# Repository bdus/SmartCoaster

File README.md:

# Smart Coaster — AI 驱动的硬件研发流水线

> 一个真实产品（智能饮水杯垫）为载体，建立 **本地 AI Agent + 参数化设计 + 自动化验证 + 数字样机可视化** 的硬件研发流程。
>
> **当前（2026-11-04，去灯 / 2 层收口轮）**：
> - **产品定义变更（以此为准）**：LED 与所有发光件全部去掉；PCB 最多 2 层。前脸只有 **26×7 屏窗 + 按键**，唯一缝隙是**顶板-底座 0.5 mm 浮动缝**（秤的行程缝）；无灯、无灯缝。
> - **P1 设计闭环**：方形 B 机械 **12 件 21/21**（37 组干涉 0）；原理图 **43 器件 / 28 网络**、ERC 0 error；**2 层 PCB 已布通：`kicad-cli pcb drc --severity-all` 0 violation / 0 unconnected**（576 track + 62 via，证据 `electronics/kicad/build/DRC_2l.rpt`；47 footprint = 43 器件 + 4 安装孔）；固件 ESP-IDF v6.1，灯效代码已删（测试计数见 `docs/HANDOFF.md`）。
> - **P2 可制造**：2 层 Gerber/钻孔/坐标/zip（`build/gerbers/`）、JLC 2 层 DFM **全 PASS**（`build/DFM.md`）、BOM（43 器件 / 24 行）；拼板建议 2×2 V-groove。
> - **P3 红点水平**：CMF 4 变体、120×120×36 包装、产品叙事、**Red Dot 2026 提交包**（`submission/`），渲染已全部按“无灯”重出。
> - **仍需用户动手**：采购 ESP32-S3-DevKitC-1 / 0.91" OLED / HY928D / HX711 模块 / 砝码，按 `docs/09` 装配并按 `tests/handboard/BRINGUP_RECORD.md` 标定；PCB 打样与 3D 打印下单。
> - **下一阶段（2026-11-04 用户新指示）**：冻结结构与功能，只做**外观变体**。功能确认：**方形 square_v1 正常（21/21，与当前电子/固件一致）**；**圆形 LUMEN 为旧概念（光导/LED/0.49" 屏/无按键）→ 不能直接当外观变体**；当前方形 PCB 对角线 131.8 mm > Ø110，**真圆需重做 PCB（功能变更）**。计划见 [`docs/13_Appearance_Variants_Plan.md`](docs/13_Appearance_Variants_Plan.md)，验收经验见 [`docs/01` §16](docs/01_AI_Hardware_Engineering_Pipeline.md)。
> - **报告与审计（2026-11-04）**：[技术报告](docs/REPORT_技术报告.md) · [成果展示](docs/REPORT_成果展示.md) · 逐条审计 [PRD](docs/AUDIT_PRD.md) / [流水线](docs/AUDIT_PIPELINE.md) / [环境](docs/AUDIT_ENV.md) · [独立验收](docs/VERIFY_REPORT.md) · **电路** [S2 仿真](docs/S2_CIRCUIT_SIM.md) / [电气评审](docs/REVIEW_ELECTRICAL.md) / [电气验证矩阵](docs/VERIFICATION_ELECTRICAL.md)
> - **EasyEDA 第二实现（2026-11-05）**：工具装到 `/data/Documents/tools/`（easyeda-agent **v1.16.0** / LCEDA Pro **4.1.97** / 官方 eprj3 skill **2.2.1**）；新建 [`electronics/easyeda/`](electronics/easyeda/README.md)，从冻结 KiCad 设计重建 `.eprj3`：**47 器件 / 7 块 / 28 网络 / 168 连接脚与 KiCad 逐脚一致**、5 门禁 + netcheck 全绿；**2 层铜（576 track + 62 via）从已验证 KiCad 布线 1:1 移植**，独立 GEOS 检查 C1–C5 全 PASS。**客户端 live DRC/铺铜/Gerber 仍被登录/激活墙阻塞**（`pro.lceda.cn` 对本机 418）；技术栈调研见 [`docs/EDA_TOOLCHAIN_SURVEY.md`](docs/EDA_TOOLCHAIN_SURVEY.md)。

## 结果一览

| 层 | 状态 |
|---|---|
| 提交包 | `submission/`：4 张主图 + A3 故事页（Red Dot 2026），无灯版 |
| 包装 | 120×120×36 天地盖 + 纸浆内衬 + 腰封；3D + 3 张渲染 |
| CMF | 4 个配色变体（Lumen Violet / Moss / Sand / Graphite）+ `render/cmf/CMF_variants.png` + `docs/10_CMF_and_Packaging.md` |
| 机械 | **方形 B 12 件 21/21**（当前功能基线，前脸 26×7 屏窗 + 按键，0.5 mm 浮动缝）；LUMEN 圆形 21/21 但为**旧概念**（含已删光导/LED、0.49" 屏、无按键），只作外观语言参考 |
| FEA | HY928D 5 kg 中心 **0.3435 mm**（k≈142.8 N/mm）、支反力 100%、+y 两颗 99.4%、非奇异热点 468 MPa |
| 电路 | ngspice：3.956 mV → 0.506 V（×128）；HX711 3.3 V 满量程 ±12.9 mV（30.7%）；**S2 四模块×六类分析 28 结果（21 PASS / 7 个真实发现）** |
| PCB | 主方案 **2 层已布通**：**43 器件 / 28 网络**（删 LED 13 + TP 6）；47 footprint、576 track + 62 via；**0 DRC / 0 unconnected**（`build/DRC_2l.rpt`）；官方 S3-MINI-1 封装（U1 与机械对齐） |
| EasyEDA 第二实现 | [`electronics/easyeda/`](electronics/easyeda/README.md)：`.eprj3`（原理图 + 已布线 2 层 PCB）47 器件 / 28 网络 / 168 连接脚与 KiCad 对账一致，5 门禁 + netcheck 全绿；铜 576 track + 62 via 由已验证 KiCad 布线移植，独立 C1–C5 几何检查全 PASS；**无铺铜 / 无客户端保存回读 / 无 Gerber**，client live 待登录；工具与限制见 [`/data/Documents/tools/EASYEDA_INSTALL_NOTES.md`](../../tools/EASYEDA_INSTALL_NOTES.md) |
| 固件 | ESP-IDF v6.1 build 通过（**519,184 B / 507 KiB**，含 NVS + NimBLE GATT 0xFF00 + 时间/跨日 + 中文 UI；删 halo 后 −13.8 KB）；host 11/11 + mock 9/9 + C↔Python 差分 16/16；PM light sleep + BLE modem sleep；**连续采样功耗预算 5.02 mA → 约 4.2 天**（S2 仿真），7 天需模拟前端占空（待固件） |
| 渲染 | Blender 4.5.3 LTS：方形 B 4 张（外观/正视/PCB 细节/爆炸图）+ CMF 4 变体 + 包装 3 张；无灯、无发光件 |
| 仿真工具 | ccx 2.22 + gmsh 4.13.1（FreeCAD 自带）、ngspice 36、QEMU 9.2.2、Blender 4.5.3 |
| IP 印花多材料 | `appearance/`：Kromacut 4.2.0 印花→多材料几何、外壳开槽、Blender 数字样机、Bambu 床面排版 3MF；**18 个可打印 STL（打印姿态：印花正面贴床/第一层、按钮躺平、无需支撑）**，140/140 只读验收 |
| 可复用 Agent 系统 | `agent-system/`：8 角色 / 28 阶段 / 7 组 145 条门禁 / 9 模板 / 脚手架 + 自校验；`check_system.py` PASS，`new_project.py` 15/15 |

## 目录

```
SmartCoaster/
├── docs/                  01 流程（含 §16 验收经验）· 02 PRD · 05–13 设计文档 · HANDOFF · AUDIT_* · VERIFY · REPORT_*
├── ref/                   原始图纸/照片/PDF + 无损 Markdown 转录
├── config/                参数与验收阈值
├── mechanical/
│   ├── lumen/             圆形 LUMEN（Ø110×17，概念线，13 零件）
│   ├── square_v1/         方形 B（100×100×18，12 零件，无灯）
│   ├── hy928d/            HY928D 传感器 v2（PROVISIONAL 重建）
│   ├── legacy/ original_cad/
├── electronics/           pinmap/电源树 · kicad/（原理图/PCB/BOM）· easyeda/（EasyEDA 第二实现）· simulation/（ngspice）
├── firmware/              model/（Python 参考）· esp32/（ESP-IDF）· wokwi/（可选）
├── simulation/            mechanical/hy928d/（FEA 网格/结果/云图）
├── tests/firmware/        C host 测试 + C↔Python 差分
├── tests/handboard/       手板 bring-up 记录表
├── submission/            Red Dot 2026 提交包（4 图 + A3 故事页）
├── render/                Blender 场景（square_b / lumen / cmf / packaging）
│   └── print/             3D 打印交付：stl/（18 个打印姿态 STL）+ appearance/（3MF/参考图/manifest）
├── appearance/            IP 印花多材料线：方法/规范/素材/印花几何/开槽/渲染/打印交付
├── agent-system/          可复用 Agent 系统：SYSTEM.yaml + roles/workflows/gates/templates/scripts
├── packaging/             包装参数化模型 + STEP/STL
├── scripts/ build/
```

## 两条产品线（几何互相独立）

| | 圆形 LUMEN | 方形 B |
|---|---|---|
| 目录 | `mechanical/lumen/` | `mechanical/square_v1/` |
| 外形 | Ø110 × 17 | 100 × 100 × 18 |
| 零件 | 13（概念线，不再推进） | **12**（13→12，删发光件） |
| 自检 | **21/21**，38 组干涉 0 | **21/21**，37 组干涉 0 |
| 特征 | 圆形概念（发光方案已废弃） | 0.91" 128×32（窗 26×7）、单键；前脸只有屏窗 + 按键，0.5 mm 浮动缝 |
| 体积/质量 | 63,796.9 mm³ / 129.8 g | 78,338.1 mm³ / 155.3 g |

> 14 mm 概念装不下 12 mm 高的 OLED 模组；普通版按 18 mm 方形，14 mm 留给极简方向。

## 快速开始

```bash
# 机械
cd mechanical/square_v1 && .venv/bin/python cad/export_v01.py && .venv/bin/python cad/verify_v01.py
cd mechanical/lumen     && .venv/bin/python cad/export_v01.py && .venv/bin/python cad/verify_v01.py

# 传感器重建
cd mechanical/hy928d && /data/Documents/tools/agentcad-venv/bin/python src/hy928d_v2.py

# 电路
cd electronics/kicad/scripts && ./build.sh            # 原理图/布线/DRC/BOM/Gerber/DFM 全流程

# 固件
bash tests/firmware/run_host_tests.sh
PYTHONPATH= /data/Documents/tools/sim-venv/bin/pytest firmware/model -q

# 渲染（无灯版）
/data/Documents/tools/blender/blender -b --python render/square_b/build_scene.py
/data/Documents/tools/blender/blender -b --python render/packaging/build_scene.py
python3 render/cmf/make_variants.py                   # 4 配色 + 拼图
python3 submission/make_story.py                      # A3 故事页（先放好 01–04 图）
```

## 关键文档

- [流程 V1.1（含仿真工程 / MCP 编排）](docs/01_AI_Hardware_Engineering_Pipeline.md)
- [产品需求 PRD](docs/02_Smart_Coaster_PRD.md)
- [可行性验证与 bring-up 计划](docs/05_Bringup_and_Verification_Plan.md)
- [固件架构（HAL + Mock + 主机测试）](docs/06_Firmware_Architecture.md)
- [B 版交互设计](docs/design/2026-11-04-ui-interaction-b-design.md)
- [CMF 与包装](docs/10_CMF_and_Packaging.md) · [产品叙事](docs/11_Product_Narrative.md)
- [HY928D 图纸转录](ref/HY928D_5kg_称重传感器_图纸转录.md) / [HX711](ref/HX711_数据手册_海芯.md) / [Hydrate 参考](ref/Hydrate_AI_拆解与结构参考.md)
- [环境安装记录](docs/环境安装记录-agentcad-freecad.md) · [两版交付说明](docs/交付说明-两个版本.md)
- [IP 印花 → 多材料一体打印（方法/工程要求）](appearance/README.md) · [3D 打印交付规范](appearance/PRINT_DELIVERY_SPEC.md)
- **一键编译**：[输入清单](appearance/INPUTS.md) · [唯一配置](appearance/config/appearance_project.yaml) · [`bash appearance/compile.sh`](appearance/compile.sh) · [Agent 提示词](appearance/AGENT_PROMPT.md)
- [可复用 Agent 系统（下一项目起点）](agent-system/README.md) · [本项目证据映射](agent-system/MAPPING_SMARTCoaster.md)

## 路线

- [产品路线：先“能用”，再“红点级”](docs/07_Product_Roadmap.md)

## 待办

- **PCB 2 层已收口**：**0 DRC / 0 unconnected**（`build/DRC_2l.rpt`）+ 2 层 Gerber/钻孔/坐标/zip（`build/gerbers/`）+ JLC 2 层 DFM 全 PASS（`build/DFM.md`）+ 布线预览 `build/pcb_2l.png`。
- 手板采购：ESP32-S3-DevKitC-1、0.91" 128×32 OLED、HY928D、HX711 模块、砝码；按 `docs/05` 矩阵测。
- 固件：BLE GATT、NVS/跨日、低功耗休眠、OLED 中文（灯效代码已删）。
- 渲染：KiCad 3D（待 3D 模型）、3D 打印参考图（拆分/方向/支撑）。

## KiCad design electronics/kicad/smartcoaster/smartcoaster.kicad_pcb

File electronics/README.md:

# electronics/

电路设计（KiCad 9.0.9）。**当前状态（2026-11-04）：43 器件 / 28 网络，ERC 0 error/0 warning；2 层 PCB 已布通，`kicad-cli pcb drc --severity-all` 0 DRC / 0 unconnected；Gerber/钻孔/坐标/DFM 已出。**

- `kicad/` KiCad 工程（原理图、网表、2 层 PCB、BOM、制造文件）——**唯一主链交付，未改动**
- `easyeda/` **EasyEDA Pro 第二实现（2026-11-05）**：`.eprj3` 原理图 + PCB placement，47 器件/28 网络/168 连接脚与 KiCad 逐脚一致；离线 5 门禁全绿，**无铜**；客户端 live 链路待登录/激活。见 [`easyeda/README.md`](easyeda/README.md)、[`easyeda/REPORT.md`](easyeda/REPORT.md)
- `kicad/scripts/` 唯一来源：`design.py`（原理图）、`gen_pcb.py`（未布线 PCB）、`route_2l.sh`（Freerouting 布线 + DRC）
- `simulation/` ngspice 网表与结果：`hy928d_frontend.cir` + `.json`（桥路 + HX711 行为前端，DC/AC；电源/噪声/蒙特卡洛仍是 GAP）
- `pinmap.md` 引脚与电源树（无 LED/光导）

关键证据：`kicad/build/DRC_2l.rpt`（0/0）、`kicad/build/ERC.rpt`（0/0）、`kicad/build/DFM.md`（JLC 2 层全 PASS）、`kicad/build/gerbers/`。

依据：`docs/02_Smart_Coaster_PRD.md` §5、`docs/HANDOFF.md`、`ref/HX711_数据手册_海芯.md` §14。

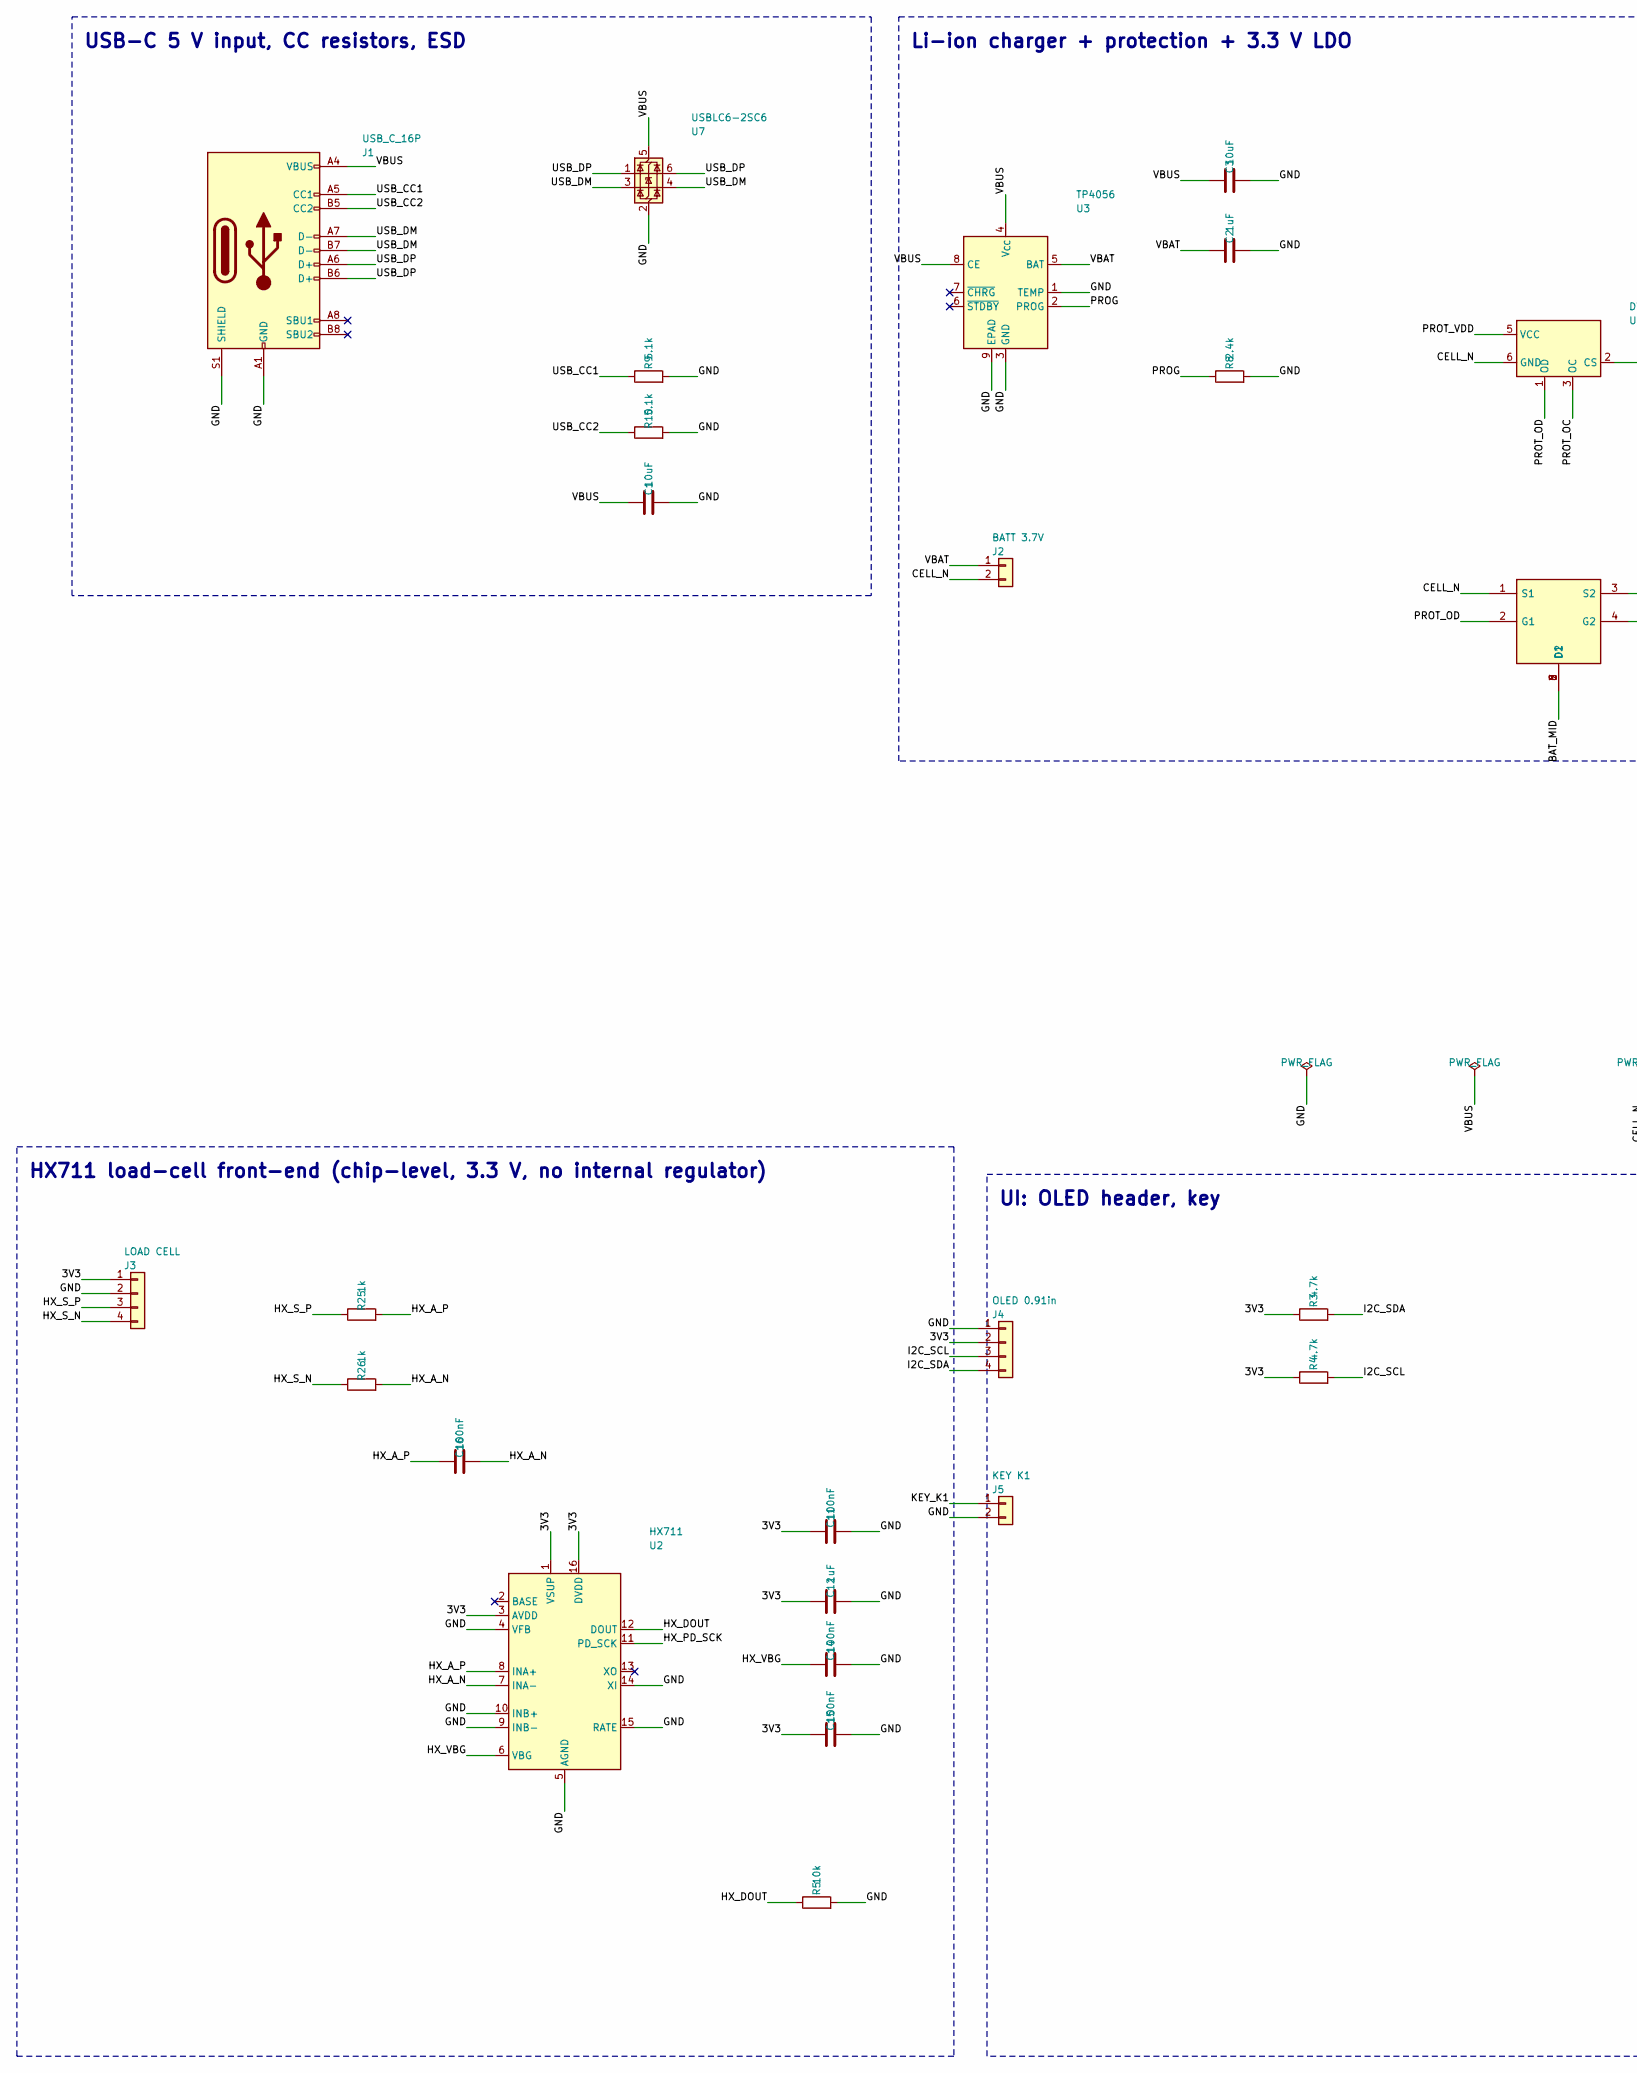
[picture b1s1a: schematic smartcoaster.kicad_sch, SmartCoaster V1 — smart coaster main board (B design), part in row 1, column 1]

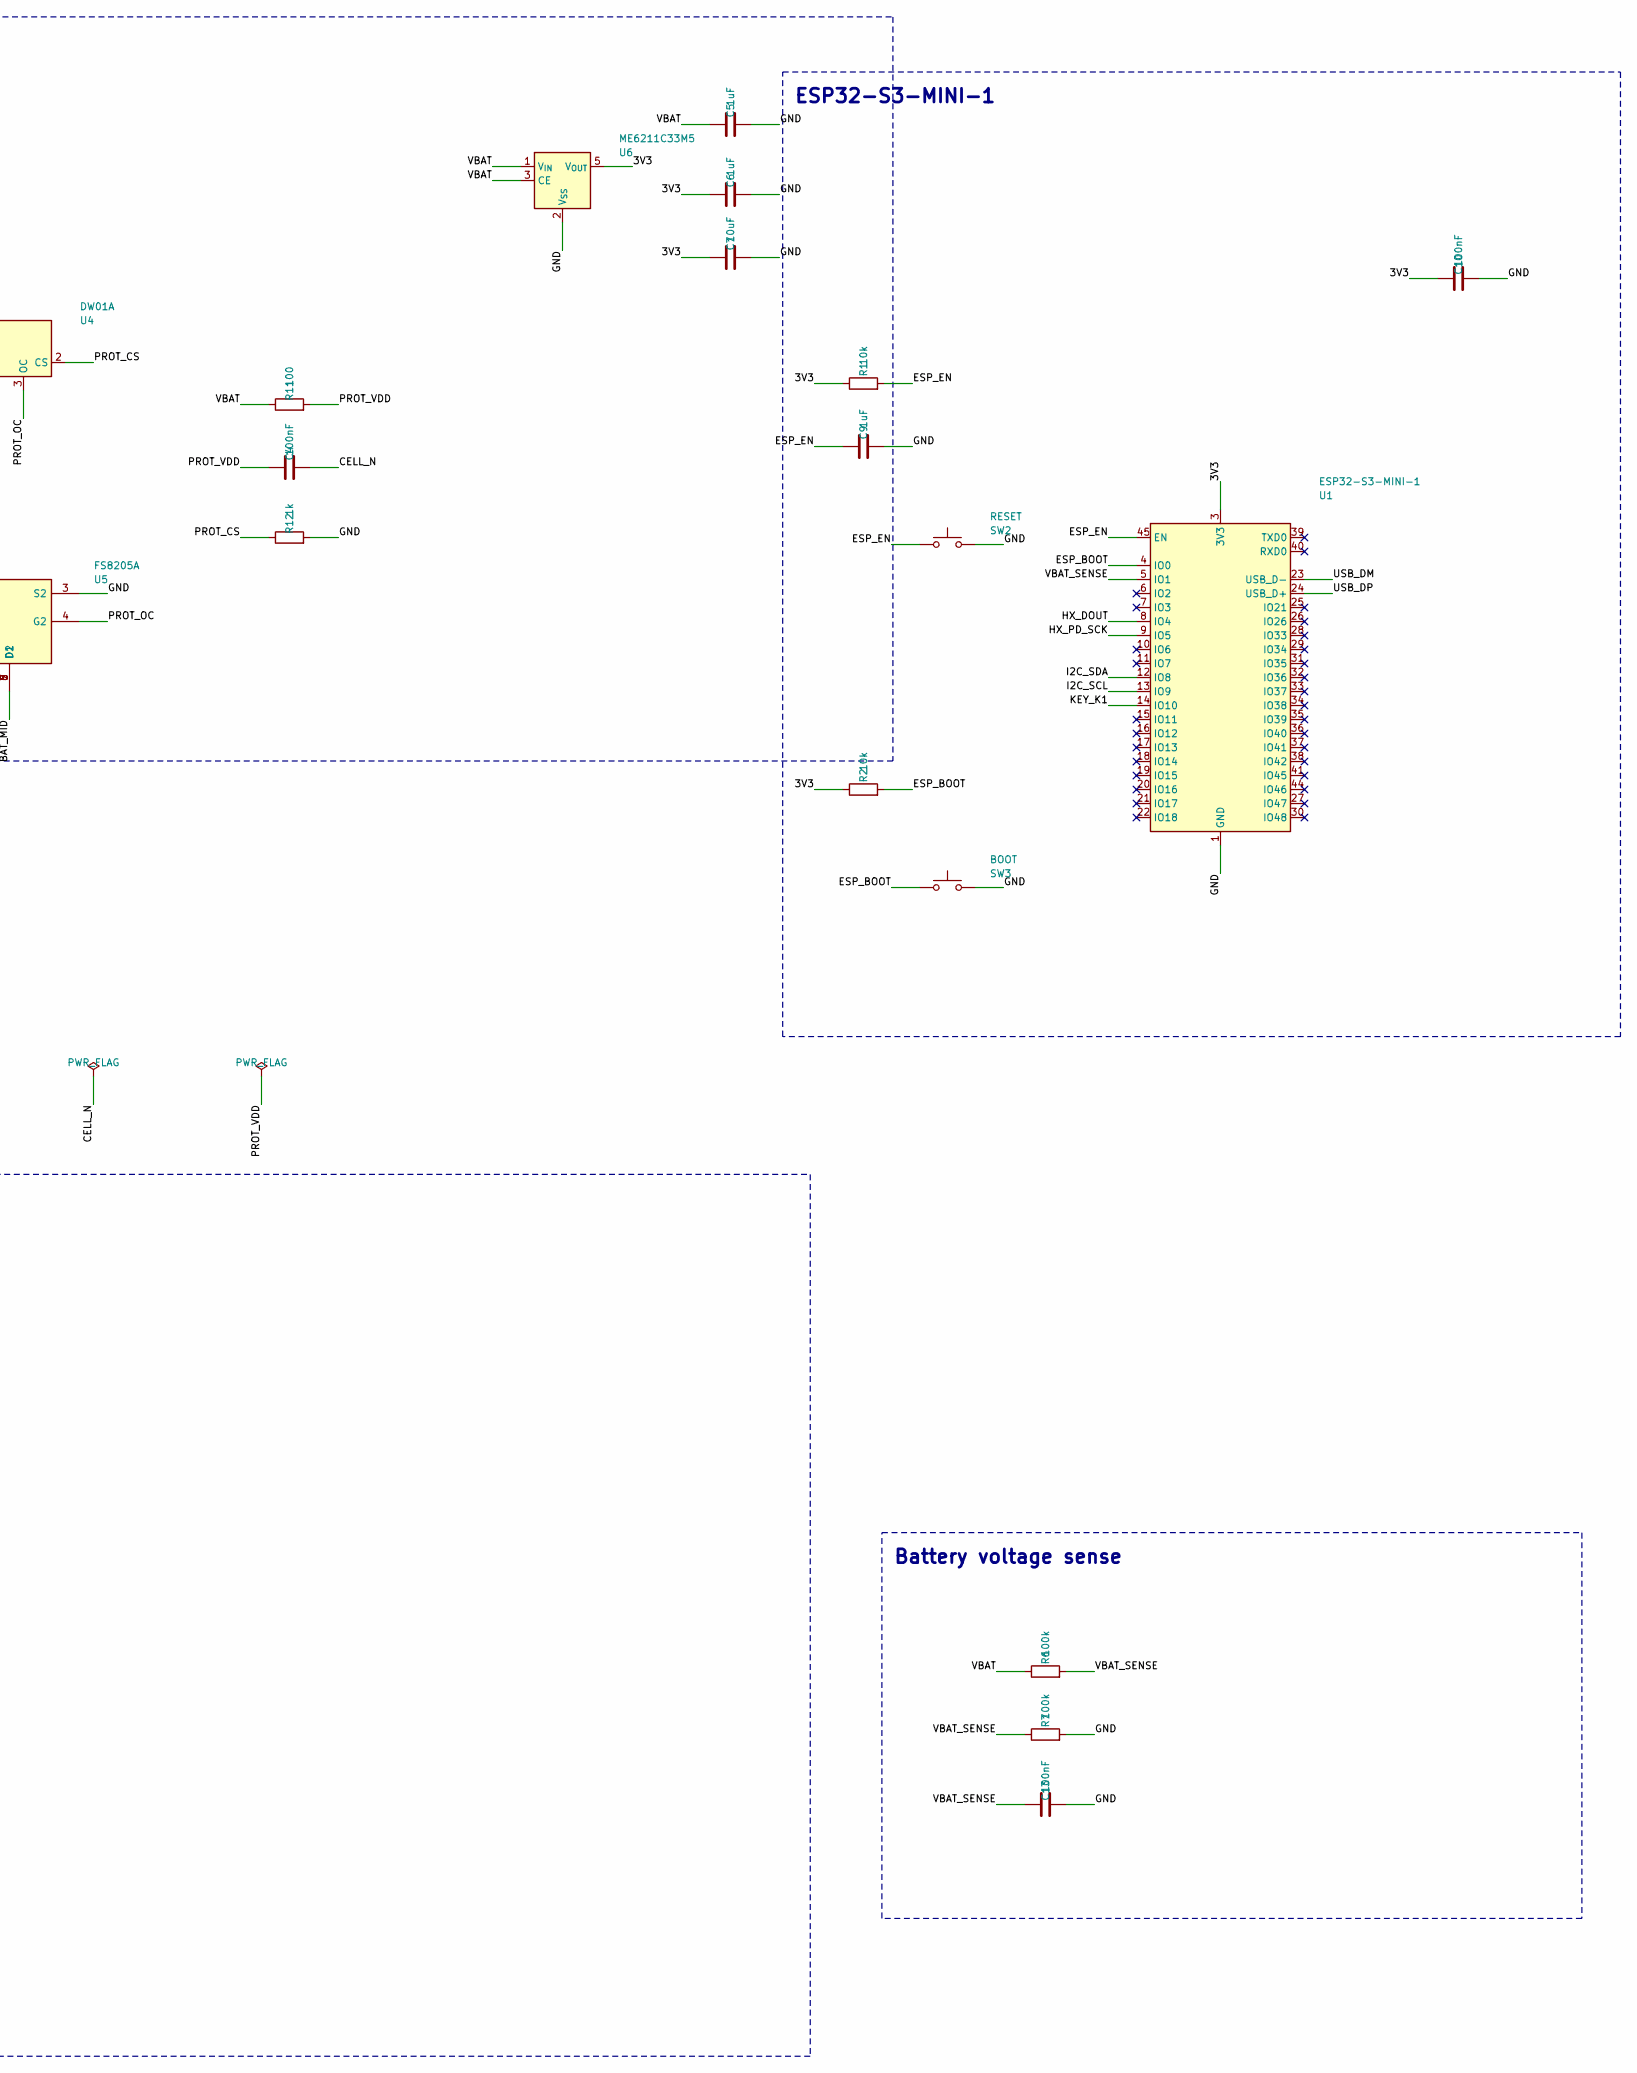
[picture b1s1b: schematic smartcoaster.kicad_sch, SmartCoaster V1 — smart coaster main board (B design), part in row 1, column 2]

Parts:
C1, C3, C7: 10uF; C_0805_2012Metric
C2, C5, C6, C9, C12: 1uF; C_0603_1608Metric
C4, C10, C11, C13, C14, C15, C16: 100nF; C_0603_1608Metric
J1: USB_C_16P; USB_C_Receptacle_HRO_TYPE-C-31-M-12
J2: BATT 3.7V; JST_PH_B2B-PH-K_1x02_P2.00mm_Vertical
J3: LOAD CELL; JST_SH_BM04B-SRSS-TB_1x04-1MP_P1.00mm_Vertical
J4: OLED 0.91in; PinHeader_1x04_P2.54mm_Vertical
J5: KEY K1; JST_PH_B2B-PH-K_1x02_P2.00mm_Vertical
R1, R2, R5: 10k; R_0603_1608Metric
R3, R4: 4.7k; R_0603_1608Metric
R6, R7: 100k; R_0603_1608Metric
R8: 2.4k; R_0603_1608Metric
R9, R10: 5.1k; R_0603_1608Metric
R11: 100; R_0603_1608Metric
R12, R25, R26: 1k; R_0603_1608Metric
SW2: RESET; SW_SPST_B3U-1000P
SW3: BOOT; SW_SPST_B3U-1000P
U1: ESP32-S3-MINI-1
U2: HX711; SOIC-16_3.9x9.9mm_P1.27mm
U3: TP4056; SOIC-8-1EP_3.9x4.9mm_P1.27mm_EP2.41x3.81mm
U4: DW01A; SOT-23-6
U5: FS8205A; SOIC-8_3.9x4.9mm_P1.27mm
U6: ME6211C33M5; SOT-23-5
U7: USBLC6-2SC6; SOT-23-6

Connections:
3V3: C6.1, C7.1, C10.1, C11.1, C12.1, C15.1, J3.1, J4.2, R1.1, R2.1, R3.1, R4.1, U1.3 (3V3), U2.1 (VSUP), U2.3 (AVDD), U2.16 (DVDD), U6.5 (V_{OUT})
BAT_MID: U5.5 (D2), U5.6 (D2), U5.7 (D1), U5.8 (D1)
CELL_N: C4.2, J2.2, U4.6 (GND), U5.1 (S1)
ESP_BOOT: R2.2, SW3.1, U1.4 (IO0)
ESP_EN: C9.1, R1.2, SW2.1, U1.45 (EN)
GND: C1.2, C2.2, C3.2, C5.2, C6.2, C7.2, C9.2, C10.2, C11.2, C12.2, C13.2, C14.2, C15.2, J1.A1 (GND), J1.A12 (GND), J1.B1 (GND), J1.B12 (GND), J1.S1 (SHIELD), J3.2, J4.1, J5.2, R5.2, R7.2, R8.2, R9.2, R10.2, R12.2, SW2.2, SW3.2, U1.1 (GND), U1.2 (GND), U1.42 (GND), U1.43 (GND), U1.46 (GND), U1.47 (GND), U1.48 (GND), U1.49 (GND), U1.50 (GND), U1.51 (GND), U1.52 (GND), U1.53 (GND), U1.54 (GND), U1.55 (GND), U1.56 (GND), U1.57 (GND), U1.58 (GND), U1.59 (GND), U1.60 (GND), U1.61 (GND), U1.62 (GND), U1.63 (GND), U1.64 (GND), U1.65 (GND), U2.4 (VFB), U2.5 (AGND), U2.9 (INB-), U2.10 (INB+), U2.14 (XI), U2.15 (RATE), U3.1 (TEMP), U3.3 (GND), U3.9 (EPAD), U5.3 (S2), U6.2 (V_{SS}), U7.2 (GND)
HX_A_N: C16.2, R26.2, U2.7 (INA-)
HX_A_P: C16.1, R25.2, U2.8 (INA+)
HX_DOUT: R5.1, U1.8 (IO4), U2.12 (DOUT)
HX_PD_SCK: U1.9 (IO5), U2.11 (PD_SCK)
HX_S_N: J3.4, R26.1
HX_S_P: J3.3, R25.1
HX_VBG: C14.1, U2.6 (VBG)
I2C_SCL: J4.3, R4.2, U1.13 (IO9)
I2C_SDA: J4.4, R3.2, U1.12 (IO8)
KEY_K1: J5.1, U1.14 (IO10)
PROG: R8.1, U3.2 (PROG)
PROT_CS: R12.1, U4.2 (CS)
PROT_OC: U4.3 (OC), U5.4 (G2)
PROT_OD: U4.1 (OD), U5.2 (G1)
PROT_VDD: C4.1, R11.2, U4.5 (VCC)
USB_CC1: J1.A5 (CC1), R9.1
USB_CC2: J1.B5 (CC2), R10.1
USB_DM: J1.A7 (D-), J1.B7 (D-), U1.23 (USB_D-), U7.3 (I/O2), U7.4 (I/O2)
USB_DP: J1.A6 (D+), J1.B6 (D+), U1.24 (USB_D+), U7.1 (I/O1), U7.6 (I/O1)
VBAT: C2.1, C5.1, J2.1, R6.1, R11.1, U3.5 (BAT), U6.1 (V_{IN}), U6.3 (CE)
VBAT_SENSE: C13.1, R6.2, R7.1, U1.5 (IO1)
VBUS: C1.1, C3.1, J1.A4 (VBUS), J1.A9 (VBUS), J1.B4 (VBUS), J1.B9 (VBUS), U3.4 (V_{CC}), U3.8 (CE), U7.5 (VBUS)

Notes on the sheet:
USB-C 5 V input, CC resistors, ESD
Li-ion charger + protection + 3.3 V LDO
ESP32-S3-MINI-1
HX711 load-cell front-end (chip-level, 3.3 V, no internal regulator)
UI: OLED header, key
Battery voltage sense

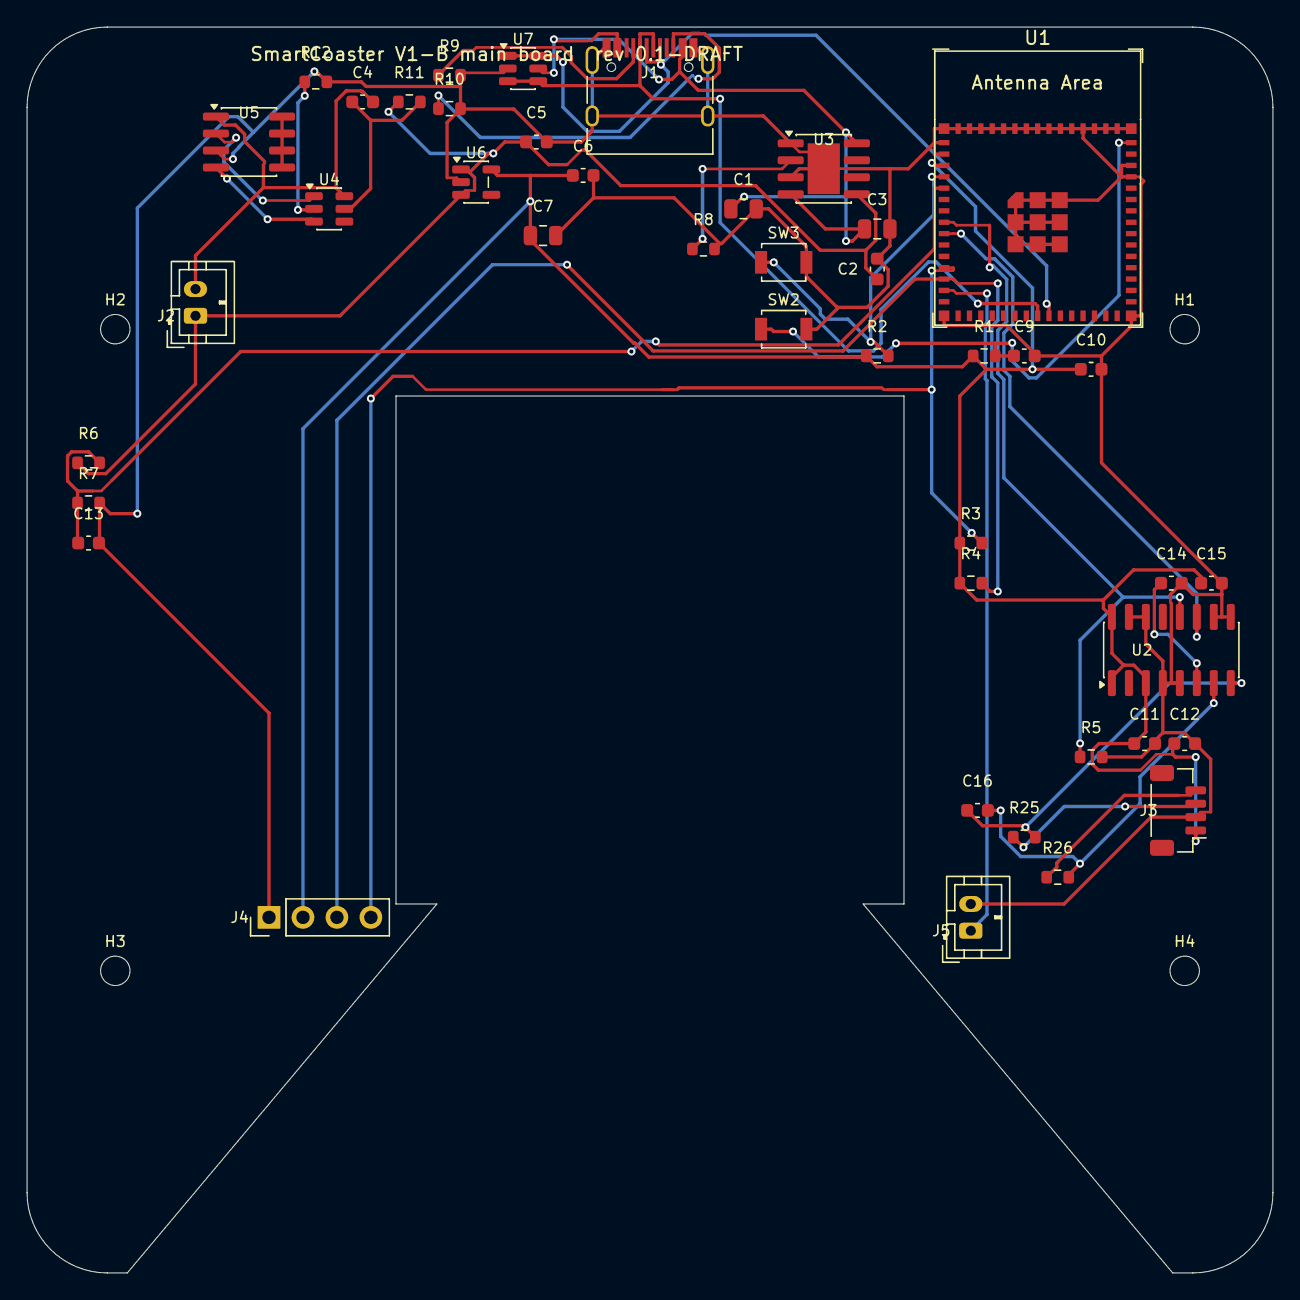
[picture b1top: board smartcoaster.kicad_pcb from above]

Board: 2 copper layers, 93.2 x 93.2 mm, 47 parts (0 on the bottom side), 28 nets.

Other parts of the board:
H1, H2, H3, H4: M2; MountingHole_2.2mm_M2

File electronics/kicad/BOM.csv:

Item,Qty,Refs,Value,MPN,Footprint,Description,Note
1,1,J1,USB_C_16P,HRO TYPE-C-31-M-12,Connector_USB:USB_C_Receptacle_HRO_TYPE-C-31-M-12,"USB-C receptacle 16P, USB 2.0, 5 V sink","16P receptacle, USB2.0 only, 5 V sink"
2,1,U7,USBLC6-2SC6,USBLC6-2SC6,Package_TO_SOT_SMD:SOT-23-6,"USB 2.0 ESD protection, 2-line, SOT-23-6","USB ESD, 2-line + VBUS"
3,2,R9 R10,5.1k,,Resistor_SMD:R_0603_1608Metric,厚膜 5.1 kΩ ±1% 1/10 W 0603,
4,3,C1 C3 C7,10uF,,Capacitor_SMD:C_0805_2012Metric,MLCC 10 µF 10 V X5R ±10% 0805,
5,1,U3,TP4056,TP4056,Package_SO:SOIC-8-1EP_3.9x4.9mm_P1.27mm_EP2.41x3.81mm,"1-cell Li-ion CC/CV charger, 4.2 V, 500 mA (Rprog 2.4k)","1 cell Li-ion CC/CV charger, 500 mA (Rprog 2.4k)"
6,5,C2 C5 C6 C9 C12,1uF,,Capacitor_SMD:C_0603_1608Metric,MLCC 1 µF 16 V X5R ±10% 0603,
7,1,R8,2.4k,,Resistor_SMD:R_0603_1608Metric,厚膜 2.4 kΩ ±1% 1/10 W 0603,Iprog = 1200/R = 500 mA
8,1,J2,BATT 3.7V,JST B2B-PH-K-S,Connector_JST:JST_PH_B2B-PH-K_1x02_P2.00mm_Vertical,"2-pin, LiPo 500 mAh with protection board","LiPo 500 mAh, JST-PH 2P"
9,1,U4,DW01A,DW01A,Package_TO_SOT_SMD:SOT-23-6,"1-cell Li-ion protection IC, SOT-23-6",1-cell protection IC
10,1,U5,FS8205A,FS8205A,Package_SO:SOIC-8_3.9x4.9mm_P1.27mm,"dual N-MOSFET, 20 V, 6 A, SOP-8, protection pair","dual N-MOSFET, common drain"
11,1,R11,100,,Resistor_SMD:R_0603_1608Metric,厚膜 100 Ω ±1% 1/10 W 0603,DW01A VDD RC filter
12,7,C4 C10 C11 C13 C14 C15 C16,100nF,,Capacitor_SMD:C_0603_1608Metric,MLCC 100 nF 25 V X7R ±10% 0603,
13,3,R12 R25 R26,1k,,Resistor_SMD:R_0603_1608Metric,厚膜 1 kΩ ±1% 1/10 W 0603,
14,1,U6,ME6211C33M5,ME6211C33M5G,Package_TO_SOT_SMD:SOT-23-5,"3.3 V LDO, 500 mA, 100 mV dropout, SOT-23-5","3.3 V 500 mA LDO, 100 mV dropout @ 300 mA"
15,1,U1,ESP32-S3-MINI-1,ESP32-S3-MINI-1-N8R2,SmartCoaster:ESP32-S3-MINI-1,"Wi-Fi/BLE SoC module, 8 MB flash, 2 MB PSRAM","8 MB flash, 2 MB PSRAM, PCB antenna; official Espressif footprint"
16,3,R1 R2 R5,10k,,Resistor_SMD:R_0603_1608Metric,厚膜 10 kΩ ±1% 1/10 W 0603,
17,1,SW2,RESET,Omron B3U-1000P,Button_Switch_SMD:SW_SPST_B3U-1000P,SMD tact switch 3x4 mm,
18,1,SW3,BOOT,Omron B3U-1000P,Button_Switch_SMD:SW_SPST_B3U-1000P,SMD tact switch 3x4 mm,
19,1,U2,HX711,HX711,Package_SO:SOIC-16_3.9x9.9mm_P1.27mm,"24-bit load-cell ADC, gain 128, 10 SPS","24-bit load-cell ADC, gain 128, 10 Hz"
20,1,J3,LOAD CELL,JST BM04B-SRSS-TB,Connector_JST:JST_SH_BM04B-SRSS-TB_1x04-1MP_P1.00mm_Vertical,"1.0 mm 4-pin, 4-wire load cell (E+/E-/S+/S-)",E+ / E- / S+ / S- (4-wire cell)
21,1,J4,OLED 0.91in,PinHeader 1x04 2.54,Connector_PinHeader_2.54mm:PinHeader_1x04_P2.54mm_Vertical,0.91in 128x32 SSD1306 I2C module header,GND / 3V3 / SCL / SDA (verify module order)
22,2,R3 R4,4.7k,,Resistor_SMD:R_0603_1608Metric,厚膜 4.7 kΩ ±1% 1/10 W 0603,
23,1,J5,KEY K1,JST B2B-PH-K-S,Connector_JST:JST_PH_B2B-PH-K_1x02_P2.00mm_Vertical,"2-pin, front-panel tact switch",front-panel tact switch (shell mounted)
24,2,R6 R7,100k,,Resistor_SMD:R_0603_1608Metric,厚膜 100 kΩ ±1% 1/10 W 0603,
